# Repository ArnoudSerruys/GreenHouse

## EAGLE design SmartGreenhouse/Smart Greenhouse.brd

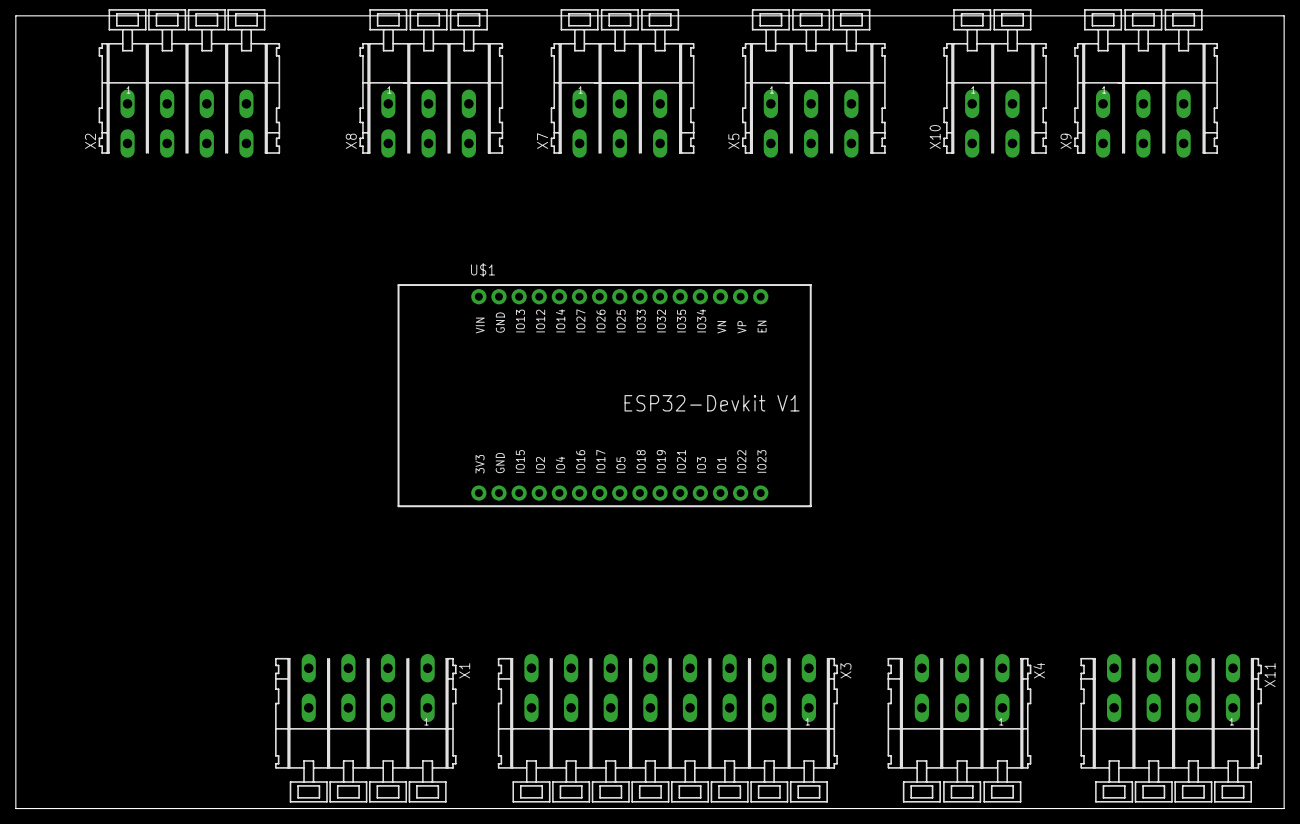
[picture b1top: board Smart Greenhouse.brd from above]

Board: 2 copper layers, 160.0 x 100.0 mm, 11 parts (0 on the bottom side), 17 nets, no tracks yet.

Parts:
U$1: ESP32DEVKITV1; ESP32-DEVKITV1
X1, X2, X11: 255-404-5
X3: 255-408-5
X4, X5, X7, X8, X9: 255-403-508
X10: 255-402-508

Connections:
unnamed: U$1.28, X3.A6, X7.A1, X8.A1, X9.A1, X10.A2
unnamed: U$1.13, X1.A1
unnamed: U$1.2, X1.A4, X2.A3, X4.A1, X5.A1, X11.A4
unnamed: U$1.12, X1.A2
unnamed: U$1.30, X1.A3, X3.A8
unnamed: U$1.24, X9.A2
unnamed: U$1.24, X3.A7
unnamed: U$1.10, X3.A4
unnamed: U$1.9, X3.A3
unnamed: U$1.11, X3.A2
unnamed: U$1.22, X8.A2
unnamed: U$1.23, X7.A2
unnamed: U$1.8, X3.A1
unnamed: U$1.27, X10.A1
unnamed: U$1.4, X2.A1
unnamed: U$1.5, X11.A2
unnamed: U$1.1, X2.A4, X4.A3, X5.A3, X7.A3, X8.A3, X9.A3, X11.A1
